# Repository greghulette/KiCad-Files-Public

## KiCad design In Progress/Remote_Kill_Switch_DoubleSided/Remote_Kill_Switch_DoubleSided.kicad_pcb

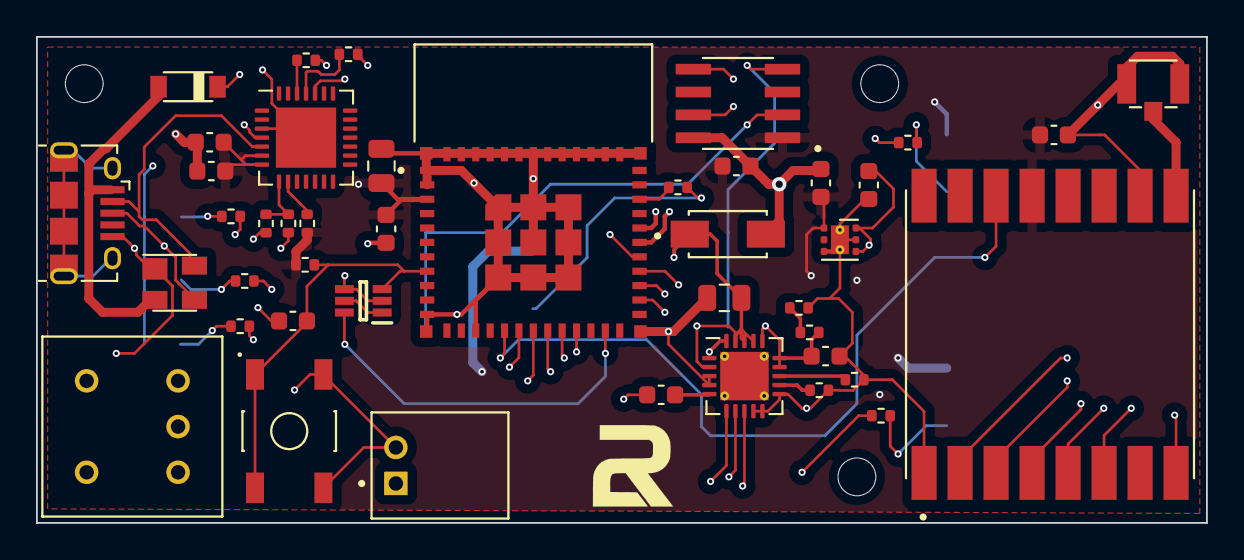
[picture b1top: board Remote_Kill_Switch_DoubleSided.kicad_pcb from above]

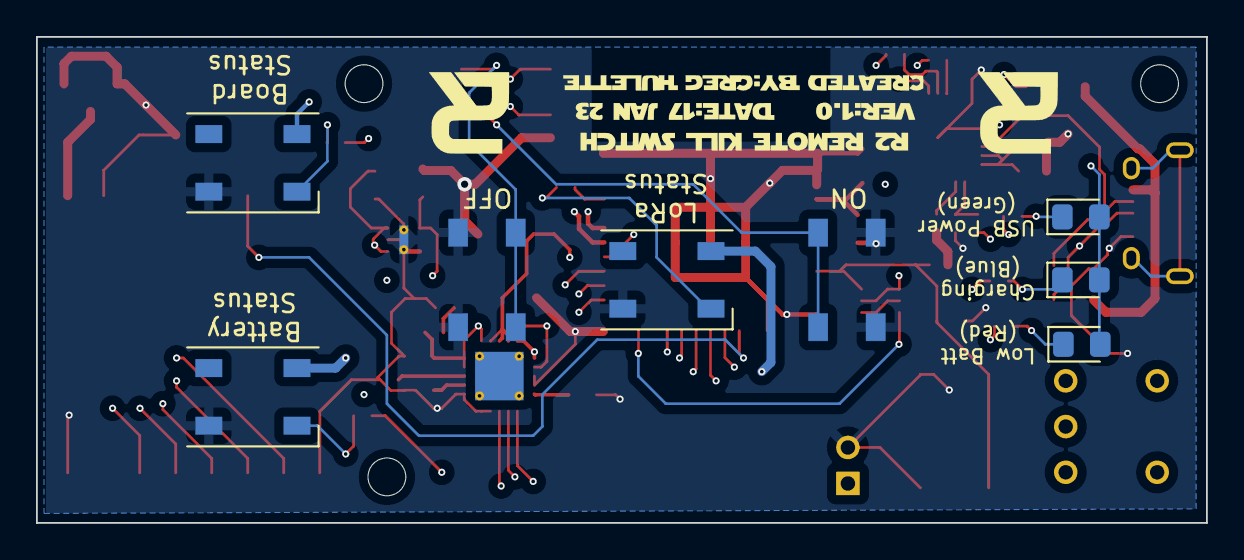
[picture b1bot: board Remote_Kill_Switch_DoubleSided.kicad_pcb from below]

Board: 4 copper layers, 65.0 x 27.0 mm, 51 parts (8 on the bottom side), 46 nets.

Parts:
C1, C8: 10uF; C_0805_2012Metric
C2, C3, C5, C10, C11: .1uF; C_0603_1608Metric
C4, C9: 4.7uF; C_0603_1608Metric
C6, C7: 1uF; C_0603_1608Metric
D1: B5819W-TP; SOD3716X135N
D2: SP0503BAHTG; SOT-143
D3: SMAJ5.0; SMAJ5.0_DIOM4325X250N
D4: Green; LED_0805_2012Metric_Pad1.15x1.40mm_HandSolder
D5: BLUE; LED_0805_2012Metric_Pad1.15x1.40mm_HandSolder
D6: Red; LED_0805_2012Metric_Pad1.15x1.40mm_HandSolder
J1: USB_B_Micro; USB_Micro-B_Amphenol_10118194_Horizontal
J2: S2B-PH-K-S(LF)(SN); JST_S2B-PH-K-S(LF)(SN)
J3: U.FL-R-SMT-1(10); HRS_U.FL-R-SMT-1(10)
L1, L2, L3: WS2812B-2020; LED_WS2812B_PLCC4_5.0x5.0mm_P3.2mm
Q2: UMH3N; SOT65P230X110-6N
R1, R10: 10K; R_0402_1005Metric
R2, R3, R6: 1K; R_0402_1005Metric
R4: 22.1K; R_0402_1005Metric
R5: 47.5K; R_0402_1005Metric
R7, R8: 82; R_0402_1005Metric
R9: 150; R_0402_1005Metric
R11, R12, R13: 100K; R_0402_1005Metric
R14, R16, R17: 470; R_0402_1005Metric
S1: TL3342F160QG; SW_TL3342F160QG
S2, S3: TL3342F160QG; KillSwiitch
SW4: AS11CH
TH1: 10K; C_0603_1608Metric
U1: ESP32-PICO-MINI-02; MODULE_ESP32-PICO-MINI-02
U2: CP2102N-A02-GQFN28; QFN-28-1EP_5x5mm_P0.5mm_EP3.35x3.35mm
U3: LP5912-3.3DRV; WSON-6-1EP_2x2mm_P0.65mm_EP1x1.6mm_ThermalVias
U4: MCP73871-2CC-Custom; QFN-20-1EP_4x4mm_P0.5mm_EP2.7x2.7mm_ThermalVias
U5: RFM95W-915S2
U6: LS18-S(Debouce); SOIC127P600X175-8N

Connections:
+3V3: C1.1, C2.1, C4.1, C5.1, C7.2, C10.1, C11.1, L1.4 (VDD), L2.4 (VDD), L3.4 (VDD), R1.1, R6.2, U1.3 (3V3), U2.6 (VDD), U2.7 (VREGIN), U3.1 (OUT), U5.13 (3.3V), U6.1 (VCC)
BATSTAT_LED_DATA: R17.2, U1.29 (IO5)
BATT_LEVEL: R12.1, R13.2
DI0_LORA: U1.16 (IO26), U5.14 (DIO0)
DTR: Q2.1 (E1), Q2.5 (B2)
GND: C1.2, C2.2, C3.2, C4.2, C5.2, C6.1, C7.1, C8.2, C9.2, C10.2, C11.2, D2.1 (A), D3.A, J1.5 (GND), J2.2, J3.1, J3.3, L1.2 (GND), L2.2 (GND), L3.2 (GND), R5.2, R10.2, R11.2, R13.1, S1.3, S1.4, S2.3, S2.4, S3.3, S3.4, TH1.2, U1.1 (GND), U1.2 (GND), U1.11 (GND), U1.14 (GND), U1.36 (GND), U1.37 (GND), U1.38 (GND), U1.39 (GND), U1.40 (GND), U1.41 (GND), U1.42 (GND), U1.43 (GND), U1.44 (GND), U1.45 (GND), U1.46 (GND), U1.47 (GND), U1.48 (GND), U1.49 (GND), U1.50 (GND), U1.51 (GND), U1.52 (GND), U1.53 (GND), U1.54 (GND), U1.55 (GND), U1.56 (GND), U1.57 (GND), U1.58 (GND), U1.59 (GND), U1.60 (GND), U1.61 (GND), U2.3 (GND), U2.29 (GND), U3.3 (PG), U3.5 (GND), U3.7 (EP), U4.3 (SEL), U4.4 (PROG2), U4.9 (TE), U4.10 (GND), U4.11 (GND), U5.1 (GND), U5.8 (GND), U5.10 (GND), U6.8 (GND)
GPIO0: Q2.6 (C1), U1.23 (IO0)
LORA_LED_DATA: R14.2, U1.26 (IO20)
MISO_LORA: U1.19 (IO12), U5.2 (MISO)
MOSI_LORA: U1.20 (IO13), U5.3 (MOSI)
NSS_LORA: U1.21 (IO15), U5.5 (NSS)
unnamed: C6.2, U3.4 (EN), U3.6 (IN), U4.1 (OUT), U4.20 (OUT)
unnamed: C9.1, R12.2, SW4.1, U4.14 (VBAT), U4.15 (VBAT), U4.16 (VBAT)
unnamed: D1.A, D2.2 (K), J1.1 (VBUS)
unnamed: D4.1 (K), R7.2
unnamed: D5.1 (K), R8.2
unnamed: J2.1, SW4.3
unnamed: J3.2, U5.9 (ANT)
unnamed: L1.3 (DI), R14.1
unnamed: L2.3 (DI), R16.1
unnamed: L3.3 (DI), R17.1
unnamed: R2.1, U2.26 (TXD)
unnamed: R3.1, U2.25 (RXD)
unnamed: R4.2, R5.1, U2.8 (VBUS)
unnamed: R6.1, U2.9 (RSTb)
unnamed: R7.1, U4.6 (PG)
unnamed: R8.1, U4.7 (STAT2)
unnamed: R9.1, U4.8 (STAT1/LBO)
unnamed: D6.1 (K), R9.2
unnamed: R10.1, U4.13 (PROG1)
unnamed: R11.1, U4.12 (PROG3)
unnamed: S2.1, S2.2, U6.2 (SW0)
unnamed: S3.1, S3.2, U6.4 (SW2)
unnamed: TH1.1, U4.5 (THERM)
OFF_SW_OUT: U1.27 (IO7), U6.5 (OUT2)
ON_SW_OUT: U1.28 (IO8), U6.7 (OUT0)
RESET: C3.1, Q2.3 (C2), R1.2, S1.1, S1.2, U1.8 (EN)
RESET_LORA: U1.17 (IO27), U5.6 (RESET)
RTS: Q2.2 (B1), Q2.4 (E2), U2.24 (RTS)
RXD0: R2.2, U1.30 (RXD0)
SCK_LORA: U1.18 (IO14), U5.4 (SCK)
STATUS_LED_DATA: R16.2, U1.33 (IO19)
TXD0: R3.2, U1.31 (TXD0)
USB_DN: D2.4 (K), J1.2 (D-), U2.5 (D-)
USB_DP: D2.3 (K), J1.3 (D+), U2.4 (D+)
VBUS: C8.1, D1.C, D3.C, D4.2 (A), D5.2 (A), D6.2 (A), R4.1, U4.2 (VPCC), U4.17 (CE), U4.18 (IN), U4.19 (IN)

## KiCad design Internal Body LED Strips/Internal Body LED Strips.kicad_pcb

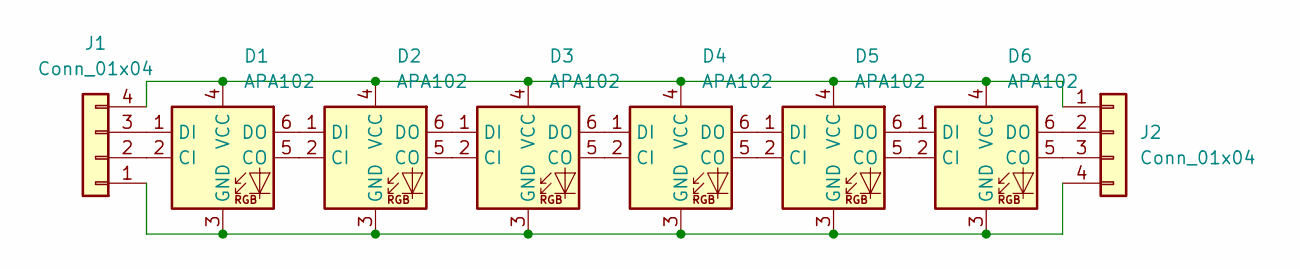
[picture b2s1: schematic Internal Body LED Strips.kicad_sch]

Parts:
D1, D2, D3, D4, D5, D6: APA102; LED_RGB_5050-6
J1, J2: Conn_01x04; PinHeader_1x04_P2.54mm_Horizontal

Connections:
unnamed: D1.1 (DI), J1.3
unnamed: D1.2 (CI), J1.2
unnamed: D1.3 (GND), D2.3 (GND), D3.3 (GND), D4.3 (GND), D5.3 (GND), D6.3 (GND), J1.1, J2.4
unnamed: D1.4 (VCC), D2.4 (VCC), D3.4 (VCC), D4.4 (VCC), D5.4 (VCC), D6.4 (VCC), J1.4, J2.1
unnamed: D1.5 (CO), D2.2 (CI)
unnamed: D1.6 (DO), D2.1 (DI)
unnamed: D2.5 (CO), D3.2 (CI)
unnamed: D2.6 (DO), D3.1 (DI)
unnamed: D3.5 (CO), D4.2 (CI)
unnamed: D3.6 (DO), D4.1 (DI)
unnamed: D4.5 (CO), D5.2 (CI)
unnamed: D4.6 (DO), D5.1 (DI)
unnamed: D5.5 (CO), D6.2 (CI)
unnamed: D5.6 (DO), D6.1 (DI)
unnamed: D6.5 (CO), J2.3
unnamed: D6.6 (DO), J2.2

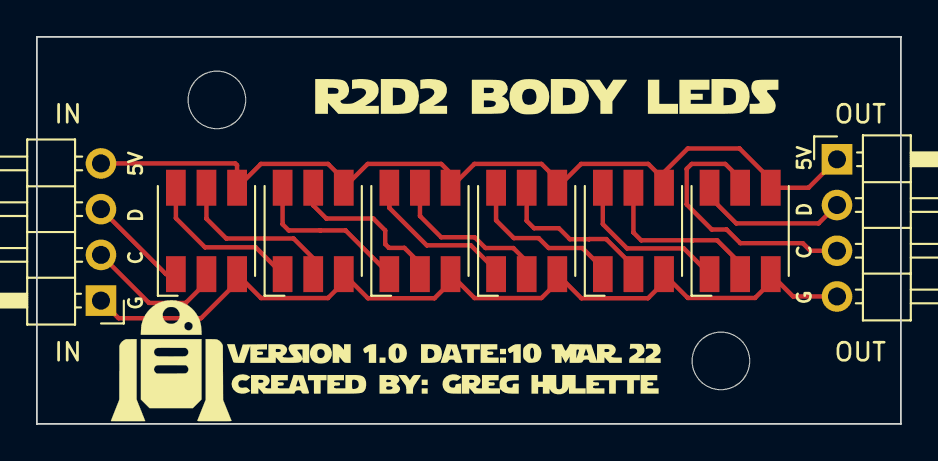
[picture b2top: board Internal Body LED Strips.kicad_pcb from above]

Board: 2 copper layers, 48.0 x 21.5 mm, 8 parts (0 on the bottom side), 16 nets.

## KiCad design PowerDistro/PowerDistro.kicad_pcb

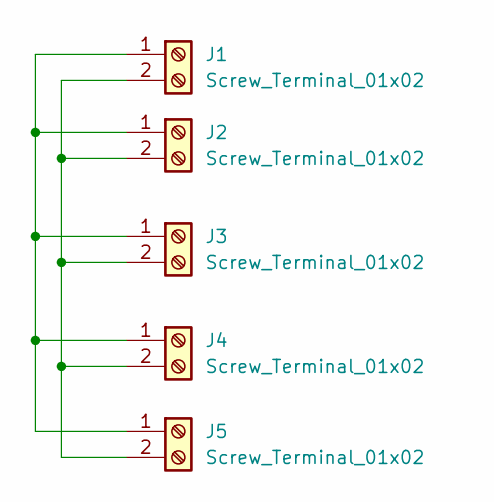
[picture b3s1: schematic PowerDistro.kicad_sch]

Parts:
J1, J2, J3, J4, J5: Screw_Terminal_01x02; TerminalBlock_bornier-2_P5.08mm

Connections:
unnamed: J1.1, J2.1, J3.1, J4.1, J5.1
unnamed: J1.2, J2.2, J3.2, J4.2, J5.2

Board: 2 copper layers, 5 parts (0 on the bottom side), 2 nets, no tracks yet.

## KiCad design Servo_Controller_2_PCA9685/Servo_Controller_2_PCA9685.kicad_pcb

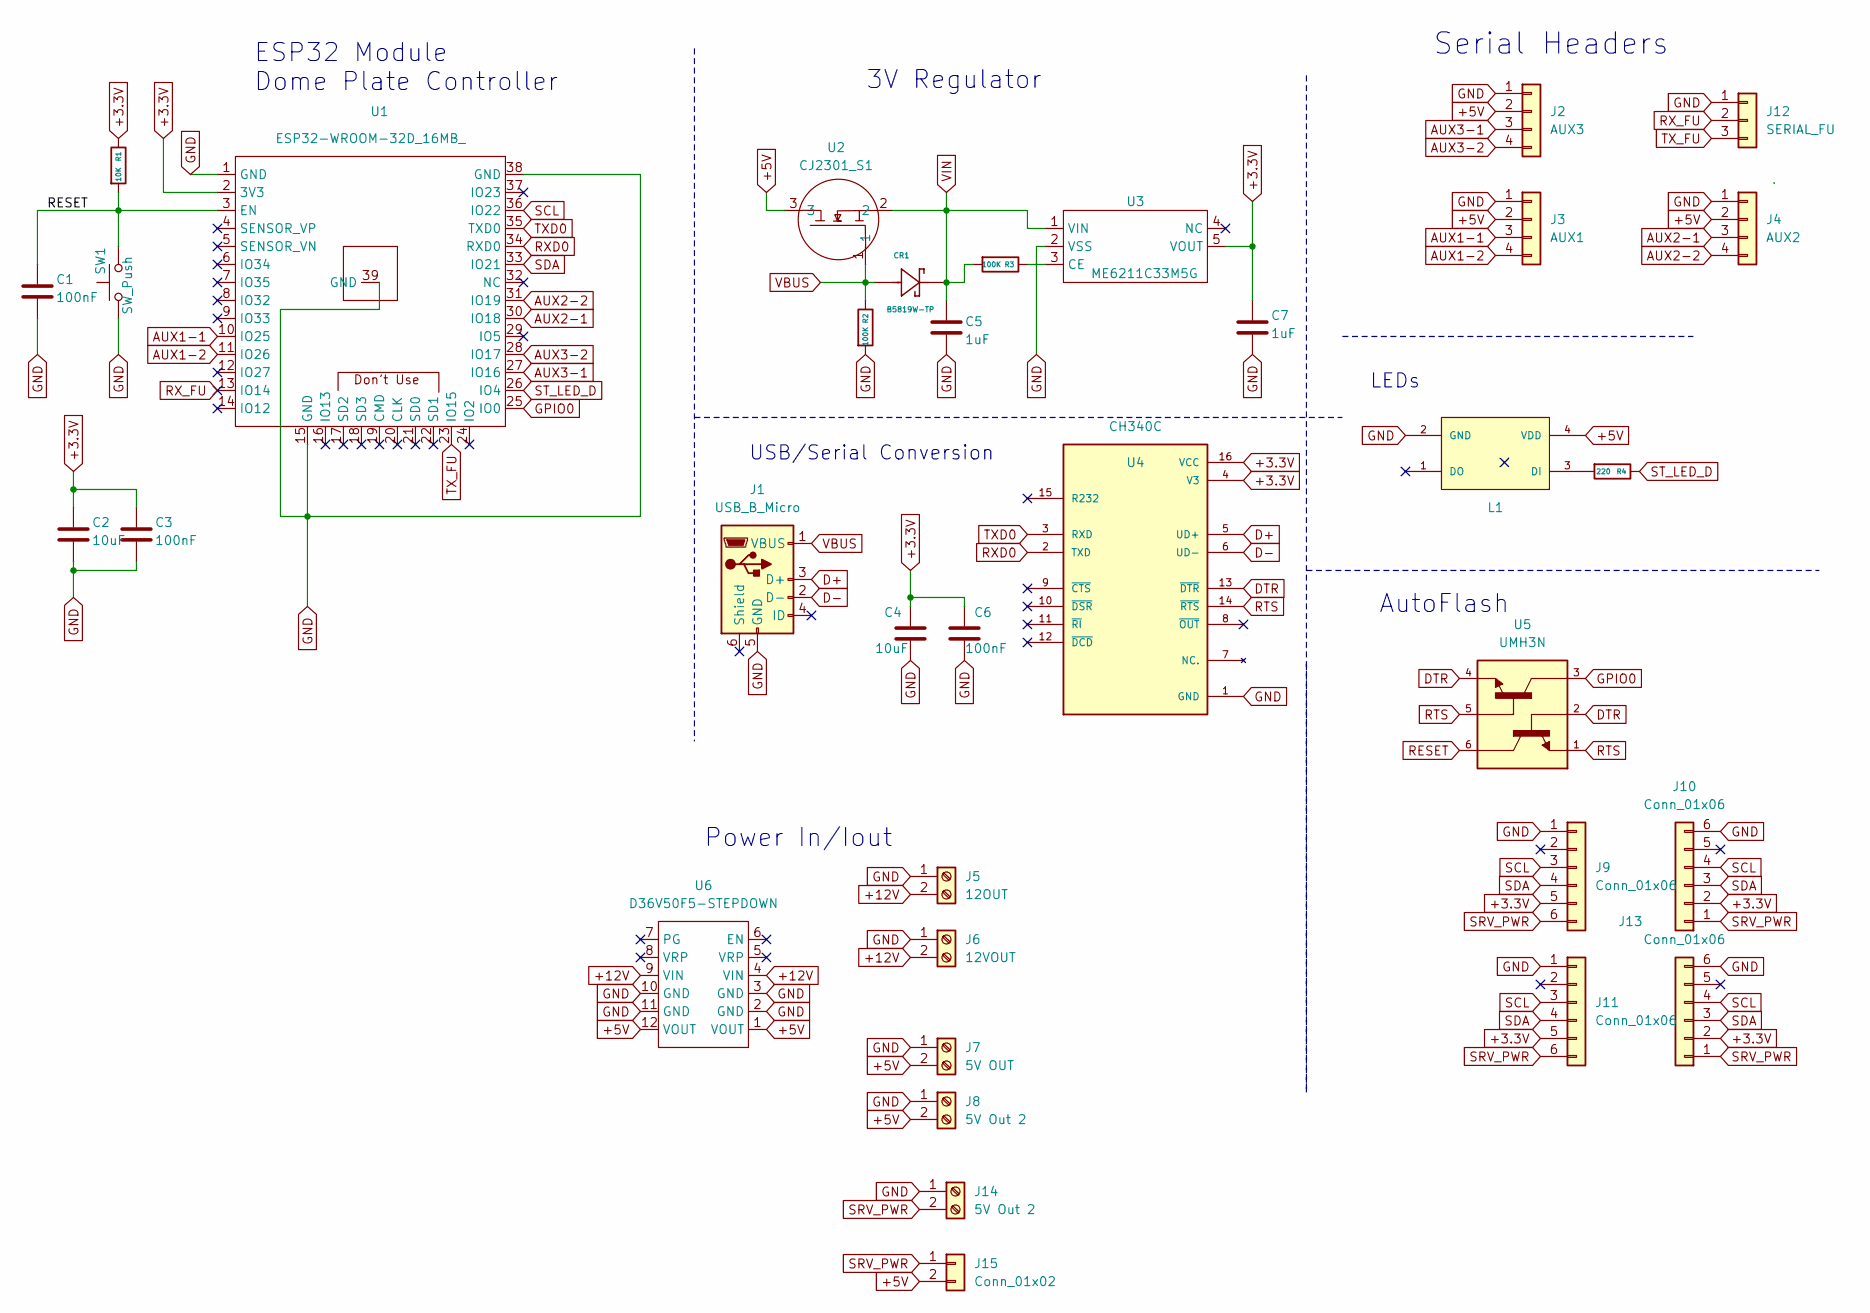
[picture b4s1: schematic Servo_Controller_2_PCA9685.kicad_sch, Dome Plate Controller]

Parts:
C1, C3, C6: 100nF; C_0402_1005Metric; LCSC C307331
C2, C4: 10uF; C_0402_1005Metric; LCSC C315248
C5, C7: 1uF; C_0402_1005Metric; LCSC C77009
CR1: B5819W-TP; SOD3716X135N; LCSC C84354
J1: USB_B_Micro; USB_Micro-B_Amphenol_10118194_Horizontal; LCSC C132563
J2: AUX3; 470531000; LCSC C240840
J3: AUX1; 470531000; LCSC C240840
J4: AUX2; 470531000; LCSC C240840
J5: 12OUT; TerminalBlock_4Ucon_1x02_P3.50mm_Horizontal; LCSC C474892
J6: 12VOUT; TerminalBlock_4Ucon_1x02_P3.50mm_Horizontal; LCSC C474892
J7: 5V OUT; TerminalBlock_4Ucon_1x02_P3.50mm_Horizontal; LCSC C474892
J8, J14: 5V Out 2; TerminalBlock_4Ucon_1x02_P3.50mm_Horizontal; LCSC C474892
J9, J10, J11, J13: Conn_01x06; PinSocket_1x06_P2.54mm_Vertical; LCSC C5224026
J12: SERIAL_FU; Molex_KK-254_AE-6410-03A_1x03_P2.54mm_Vertical; LCSC C471416
J15: Conn_01x02; PinHeader_1x02_P2.54mm_Vertical
L1: WS2812B-2020; LCSC C965555
R1: 10K; R_0603_1608Metric; LCSC C269701
R2, R3: 100K; R_0603_1608Metric; LCSC C25803
R4: 220; R_0402_1005Metric; LCSC C25091
SW1: SW_Push; TS-1101S-B-B-B-W-A; LCSC C692465
U1: ESP32-WROOM-32D_16MB_; ESP32-WROOM-32; LCSC C529578
U2: CJ2301_S1; SOT-23; LCSC C8547
U3: ME6211C33M5G; SOT-23-5; LCSC C82942
U4: CH340C; SOIC127P600X180-16N; PARTREV 2G; LCSC C84681
U5: UMH3N; UMT6; LCSC C62892
U6: D36V50F5-STEPDOWN

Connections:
+3.3V: C2.1, C3.1, C4.1, C6.1, C7.1, J9.5, J10.2, J11.5, J13.2, R1.1, U1.2 (3V3), U3.5 (VOUT), U4.4 (V3), U4.16 (VCC)
+5V: J2.2, J3.2, J4.2, J7.2, J8.2, J15.2, L1.4 (VDD), U2.3, U6.1 (VOUT), U6.12 (VOUT)
+12V: J5.2, J6.2, U6.4 (VIN), U6.9 (VIN)
AUX1-1: J3.3, U1.10 (IO25)
AUX1-2: J3.4, U1.11 (IO26)
AUX2-1: J4.3, U1.30 (IO18)
AUX2-2: J4.4, U1.31 (IO19)
AUX3-1: J2.3, U1.27 (IO16)
AUX3-2: J2.4, U1.28 (IO17)
D+: J1.3 (D+), U4.5 (UD+)
D-: J1.2 (D-), U4.6 (UD-)
DTR: U4.13 (~DTR), U5.2, U5.4
GND: C1.2, C2.2, C3.2, C4.2, C5.1, C6.2, C7.2, J1.5 (GND), J2.1, J3.1, J4.1, J5.1, J6.1, J7.1, J8.1, J9.1, J10.6, J11.1, J12.1, J13.6, J14.1, L1.2 (GND), R2.2, SW1.1, U1.1 (GND), U1.15 (GND), U1.38 (GND), U1.39 (GND), U3.2 (VSS), U4.1 (GND), U6.2 (GND), U6.3 (GND), U6.10 (GND), U6.11 (GND)
GPIO0: U1.25 (IO0), U5.3
unnamed: L1.3 (DI), R4.2
unnamed: R3.1, U3.3 (CE)
RESET: C1.1, R1.2, SW1.2, U1.3 (EN), U5.6
RTS: U4.14 (~RTS), U5.1, U5.5
RXD0: U1.34 (RXD0), U4.2 (TXD)
RX_FU: J12.2, U1.13 (IO14)
SCL: J9.3, J10.4, J11.3, J13.4, U1.36 (IO22)
SDA: J9.4, J10.3, J11.4, J13.3, U1.33 (IO21)
SRV_PWR: J9.6, J10.1, J11.6, J13.1, J14.2, J15.1
ST_LED_D: R4.1, U1.26 (IO4)
TXD0: U1.35 (TXD0), U4.3 (RXD)
TX_FU: J12.3, U1.23 (IO15)
VBUS: CR1.A, J1.1 (VBUS), R2.1, U2.1
VIN: C5.2, CR1.C, R3.2, U2.2, U3.1 (VIN)

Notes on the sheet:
ESP32 Module Dome Plate Controller
3V Regulator
LEDs
Power In/Iout
USB/Serial Conversion
AutoFlash
Serial Headers

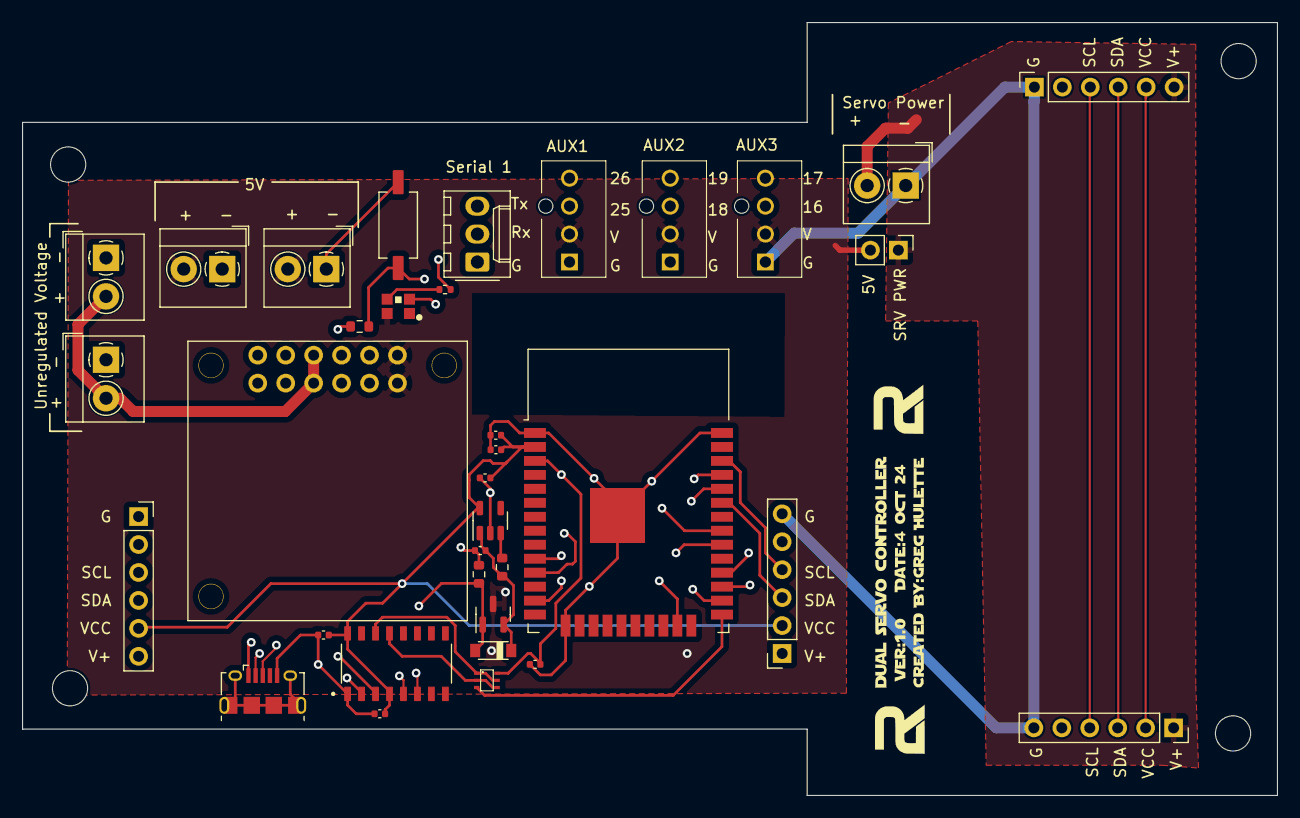
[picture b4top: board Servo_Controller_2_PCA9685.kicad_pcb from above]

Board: 4 copper layers, 114.1 x 70.2 mm, 35 parts (0 on the bottom side), 28 nets.

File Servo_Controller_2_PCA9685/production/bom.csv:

Designator,Footprint,Quantity,Value,LCSC Part #
"C1, C3, C6",0402,3,100nF,C307331
"C2, C4",0402,2,10uF,C315248
"C5, C7",0402,2,1uF,C77009
CR1,SOD3716X135N,1,B5819W-TP,C84354
J1,USB_Micro-B_Amphenol_10118194_Horizontal,1,USB_B_Micro,C132563
"J10, J11, J13, J9",PinSocket_1x06_P2.54mm_Vertical,4,Conn_01x06,C5224026
J12,Molex_KK-254_AE-6410-03A_1x03_P2.54mm_Vertical,1,SERIAL_FU,C471416
"J14, J8",TerminalBlock_4Ucon_1x02_P3.50mm_Horizontal,2,5V Out 2, C474892
J15,PinHeader_1x02_P2.54mm_Vertical,1,Conn_01x02,
J2,470531000,1,AUX3,C240840 
J3,470531000,1,AUX1,C240840 
J4,470531000,1,AUX2,C240840 
J5,TerminalBlock_4Ucon_1x02_P3.50mm_Horizontal,1,12OUT, C474892
J6,TerminalBlock_4Ucon_1x02_P3.50mm_Horizontal,1,12VOUT, C474892
J7,TerminalBlock_4Ucon_1x02_P3.50mm_Horizontal,1,5V OUT, C474892
L1,WS2812B-2020,1,WS2812B-2020,C965555
R1,0603,1,10K,C269701
"R2, R3",0603,2,100K,C25803
R4,0402,1,220,C25091
SW1,TS-1101S-B-B-B-W-A,1,SW_Push, C692465
U1,ESP32-WROOM-32,1,ESP32-WROOM-32D_16MB_, C529578
U2,SOT-23,1,CJ2301_S1, C8547
U3,SOT-23-5,1,ME6211C33M5G,C82942
U4,SOIC127P600X180-16N,1,CH340C,C84681
U5,UMT6,1,UMH3N, C62892
U6,D36V50F5-STEPDOWN,1,D36V50F5-STEPDOWN,

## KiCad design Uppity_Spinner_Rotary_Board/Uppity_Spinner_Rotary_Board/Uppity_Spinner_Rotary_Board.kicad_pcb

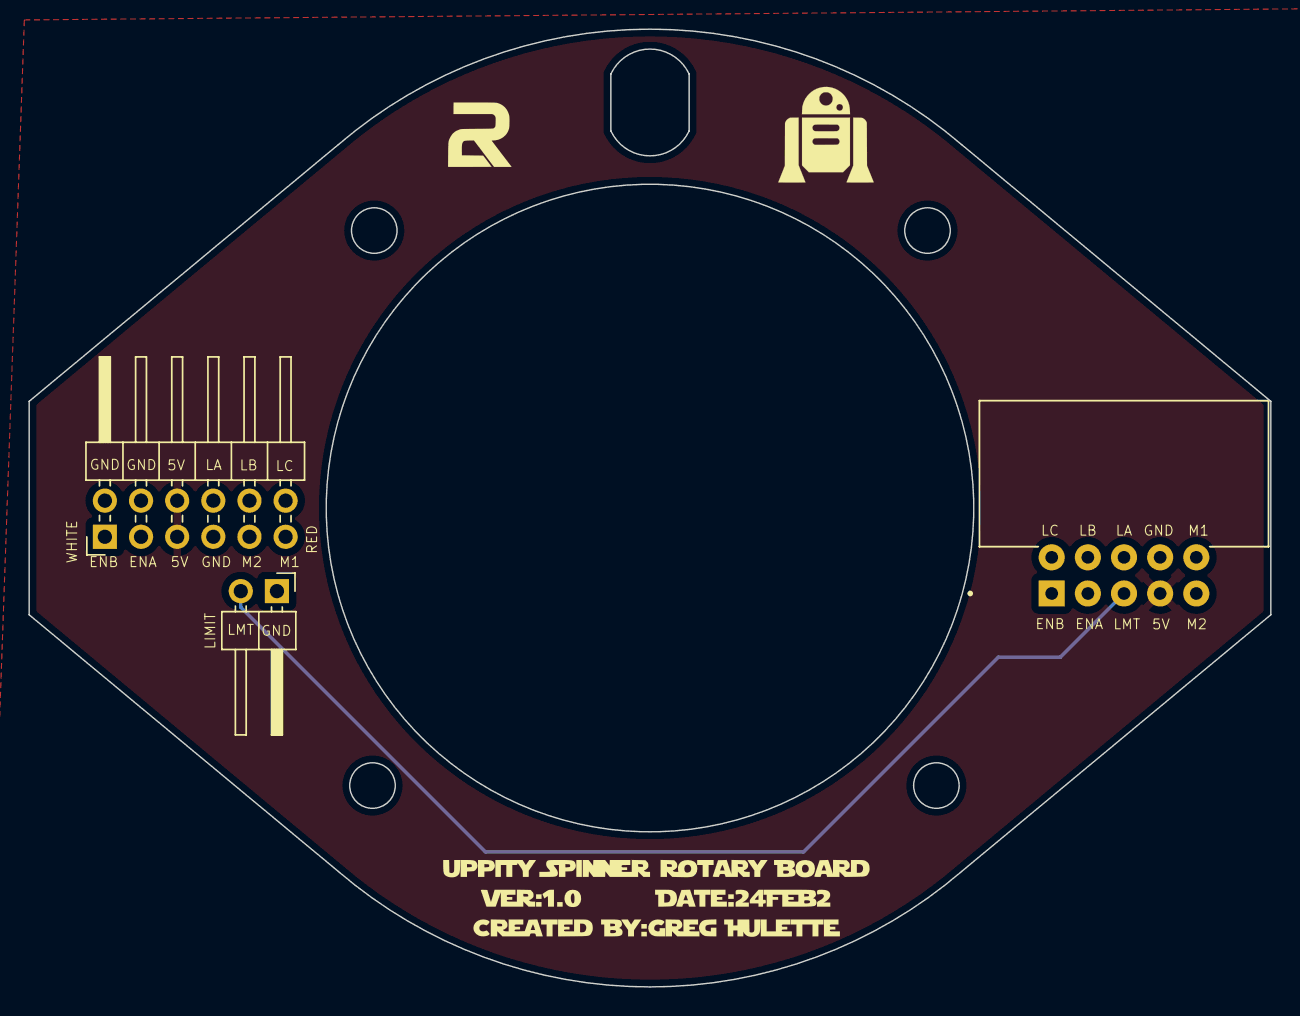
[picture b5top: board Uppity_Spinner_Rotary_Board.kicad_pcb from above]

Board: 4 copper layers, 87.2 x 67.3 mm, 3 parts (0 on the bottom side), 10 nets.

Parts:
J1: Motor Lights; PinHeader_2x06_P2.54mm_Horizontal
J2: Lifter Board Connector; TE_1761607-3Uppity
J3: Limit; PinHeader_1x02_P2.54mm_Horizontal

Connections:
5V: J1.5, J1.6, J2.7
GND: J1.2, J1.4, J1.7, J2.8, J3.1
LKIT_A: J1.8, J2.6
LKIT_B: J1.10, J2.4
LKIT_C: J1.12, J2.2
RMOT1: J1.9, J2.10
RMOT2: J1.11, J2.9
RTR_ENA: J1.3, J2.3
RTR_ENB: J1.1, J2.1
RTR_LIMIT: J2.5, J3.2
